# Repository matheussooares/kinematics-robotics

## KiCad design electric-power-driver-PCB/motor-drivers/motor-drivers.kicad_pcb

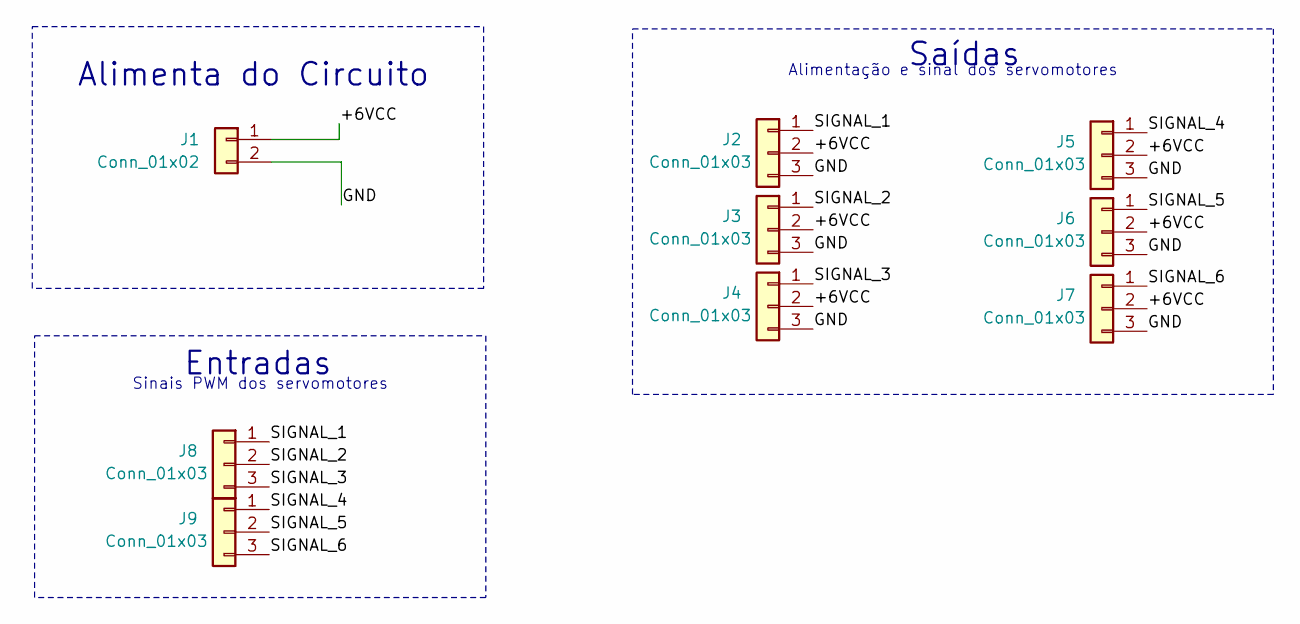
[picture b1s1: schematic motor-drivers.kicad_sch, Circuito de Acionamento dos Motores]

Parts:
J1: Conn_01x02; TerminalBlock_philmore_TB132
J2, J3, J4, J5, J6, J7, J8, J9: Conn_01x03; TerminalBlock_philmore_TB133

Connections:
/+6VCC: J1.1, J2.2, J3.2, J4.2, J5.2, J6.2, J7.2
/GND: J1.2, J2.3, J3.3, J4.3, J5.3, J6.3, J7.3
/SIGNAL_1: J2.1, J8.1
/SIGNAL_2: J3.1, J8.2
/SIGNAL_3: J4.1, J8.3
/SIGNAL_4: J5.1, J9.1
/SIGNAL_5: J6.1, J9.2
/SIGNAL_6: J7.1, J9.3

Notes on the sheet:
Alimentação e sinal dos servomotores
Sinais PWM dos servomotores
Alimenta do Circuito
Entradas
Saídas

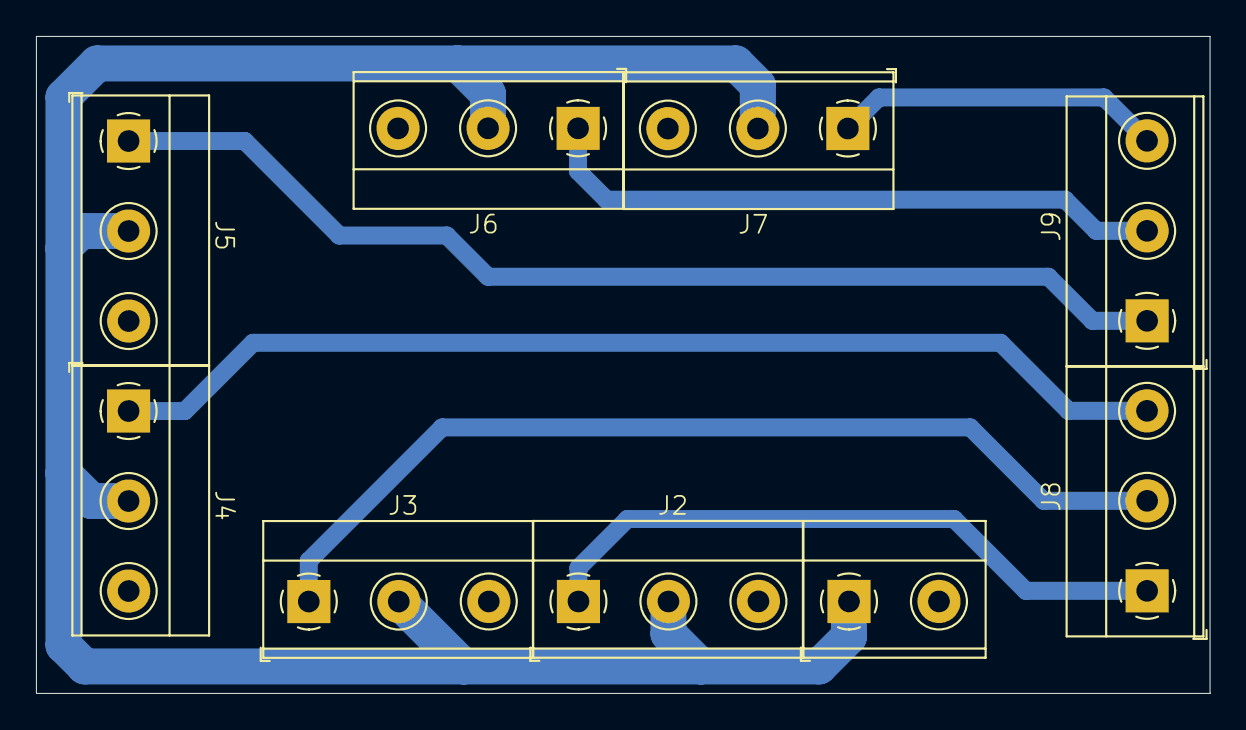
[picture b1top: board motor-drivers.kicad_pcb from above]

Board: 2 copper layers, 65.2 x 36.5 mm, 9 parts (0 on the bottom side), 8 nets.

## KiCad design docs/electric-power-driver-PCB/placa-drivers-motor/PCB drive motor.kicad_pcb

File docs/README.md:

# Cinemática de um robô didático

O cálculo da cinemática inversa é um desafio na robótica, especialmente para manipuladores robóticos, e métodos tradicionais muitas vezes não são eficazes.
Este trabalho foca na solução da cinemática inversa de um robô manipulador didático com 5 graus de liberdade (DoF), disponível no laboratório da UFC, utilizando algoritmos de aprendizado de máquina com foco em abordagens de modelos locais e globais.

Especificamente, foram empregadas redes neurais Perceptron Multicamadas e o algoritmo K-means para os modelos locais segmentarem o espaço operacional. Inicialmente, a modelagem da cinemática direta é  realizada, utilizando a notação de Denavit-Hartenberg, de modo a gerar um banco de dados contendo informações do espaço cartesiano e do espaço das juntas do manipulador. Este banco de dados é então filtrado, removendo amostras inalcançáveis e amostras próximas entre si no  espaço cartesiano. A fase de otimização de hiperparâmetros para os modelos globais envolveu ajustar a melhor arquitetura das redes neurais, e para os modelos locais abrangeu determinar o número ````k```` de clusters que melhor dividisse o espaço operacional. A avaliação de desempenho dos algoritmos é feita com base nas medidas ````R²```` e ````MSE````, tanto no espaço das juntas como no espaço cartesiano, e os resultados obtidos evidenciam que ambas as abordagens se mostraram viáveis para a tarefa em questão, com a abordagem local superando a global.

## Requisitos

````
pip install -r requirements.txt
````

## Objetivo

O objetivo geral do trabalho consiste na aproximação da cinemática inversa de um robô manipulador didático através de algoritmos de aprendizado de máquina. Por isso, os seguintes objetivos específicos foram traçados:

- Estudar métodos para geração da cinemática direta de um manipulador robótico;
- Investigar dados relevantes que relacionem os ângulos das juntas com a posição cartesianas para fins de treinamento dos modelos de aprendizado de máquina;
- Pesquisar modelos de regressão para aproximação de cinemática inversa; 
- Investigar métodos de avaliação para os modelos que solucionam a cinemática inversa.

## Máterias e métodos

O braço robótico trata-se de um robô do tipo manipulador, desenvolvido em um módulo didático pelo grupo de pesquisa em robótica do [IFCE](https://robotica.ifce.edu.br/). Sua fabricação foi realizada por meio de uma impressora 3D, utilizando filamento de PLA, um material de baixo custo amplamente empregado em impressões tridimensionais.

<div align="center">
  
  <br>
  <em>Figura 1: Braço robótico didático</em>
</div>

### Modelagem Direta do Manipulador

A estrutura mecânica do braço é composta por cinco partes físicas interligadas por cinco juntas rotacionais (5 GDL), definindo o robô como um modelo 5𝑅.

<div align="center">
  
  <br>
  <em>Figura 2: Estrutura do braço robótico didático</em>
</div>

Devido ao mecanismo robótico ser constituido por 5 graus de liberdade de juntas rotativas, a cadeia cinemática possui cinco variáveis de juntas $\theta_{i}$, para $i = 1,...,5$. Utilizando as regras e etapas do método de Denavit-Hartenberg são fixados os sistemas de referência locais em cada elemento do robô e levantado os seus parâmetro D-H.

<div align="center">
  
  <br>
  <em>Figura 3: Sistema de coordenadas locais do manipulador didático</em>
</div>

A descrição da cinemática direta desse sistema está apresentada na Tabela abaixo, no qual define os parâmetros de Denavit-Hartenberg de cada elemento do manipulador.

| i | $\theta$ ($^\circ$) | $a$ ($cm$) | $d$ ($cm$) | $\alpha$ ($^\circ$) |
|---|----------------------|------------|------------|---------------------|
| 1 | $\theta_{1}$         | $0$         | $Elo_{0}$      | $+90$           |
| 2 | $\theta_{2}$         | $Elo_{1}$      | $0$           | $+180$        |
| 3 | $\theta_{3}$         | $Elo_{2}$      | $0$           | $-180$        |
| 4 | $\theta_{4} + 90$    | $0$           | $0$           | $+90$          |
| 5 | $\theta_{5}$         | $0$           | $Elo_{3}+ Elo_{4}$ | $0$       |

A validação da cinemática direta foi conduzida inserindo a parametrização D-H no modelo do braço robótico desenvolvido na biblioteca Robotics Toolbox for Python.

<div align="center">
  
  <br>
  <em>Figura 4: Simulação da modelagem direta do manipulador didático</em>
</div>

### Padrões de Treinamento

O método para geração dos padrões de treinamento passa pela modelagem da cinemática direta do manipulador. A base de dados representa todo o volume de trabalho e o comportamento dos ângulos das juntas do robô realizando o mapeamento das relações entre o espaço operacional e o espaço das juntas.

<div align="center">
  
  <br>
  <em>Figura 5: Volume de trabalho do manipulador didático</em>
</div>

A base de dados bruta possui $33275$ observações. A decisão de fixar $\theta_{5}=0$, por influenciar na orientação do efetuador, simplificou a geração dos padrões. A distribuição no número de amostras por junta 𝑁 permitiu uma cobertura eficaz dos eixos. O ângulo $\theta_{1}$ otimizou a exploração do espaço $(𝑥,𝑦)$ e os outros ângulos balancearam o eixo $𝑧$. Considerando $𝑁 = 25$ obteve-se um total de $456976$ amostras. Com as resoluções houve uma redução de $91,5\%$;

A ausência de tratamento nos dados pode gerando a construção de modelos pouco fiéis, aumento dos custos computacionais e dificuldade do modelo em entender os padrões de treinamento (Faceli, 2011). E por conta dos aspectos não lineares, as singularidades e as soluções mal postas das equações, levantarem a existências de múltiplas soluções, nenhuma solução ou soluções não admissíveis nas posições do efetuador (MELO, 2015), é definido um conjunto de pré-processamento dos dados.

Para um raio de similaridade de $𝑟_{𝑠}=1 𝑐𝑚$, a base de dados final passou a conter $6890$ amostras, representando uma redução de 20,7% dos dados originais. Contêm atributos de entradas que descrevem a posição $(𝑥,𝑦,𝑧)$ e as orientações Roll, Pitch e Yaw (𝜑,𝛽,𝜓) do efetuador no espaço tridimensional.

<div align="center">
  
  <br>
  <em>Figura 6: Volume de trabalho do manipulador sem redundâncias</em>
</div>

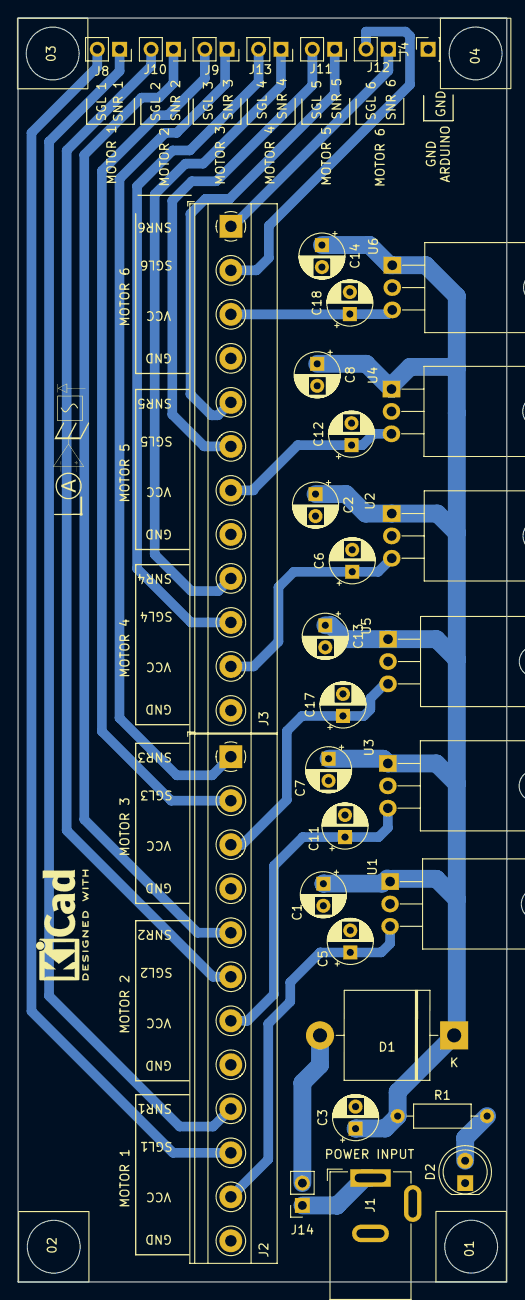
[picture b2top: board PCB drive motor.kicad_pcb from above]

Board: 2 copper layers, 55.5 x 143.6 mm, 37 parts (0 on the bottom side), 23 nets.

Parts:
01, 02, 03, 04: Furo
C1, C2, C7, C8, C13, C14: 10uF/50V; CP_Radial_D5.0mm_P2.50mm
C3, C5, C6, C11, C12, C17, C18: 1uF/50V; CP_Radial_D5.0mm_P2.50mm
D1: 1N5404; D_DO_6A6_DC__P15.24mm_Horizontal_D1.0mm
D2: LED; LED_D5.0mm
J1: CONN_ALIMENTAÇÃO_12V; BarrelJack_GCT_DCJ200-10-A_Horizontal
J2: Conn_motores_01_03; TerminalBlock_Phoenix_MKDS-1,5-12_1x12_P5.00mm_Horizontal
J3: Conn_motores_04_06; TerminalBlock_Phoenix_MKDS-1,5-12_1x12_P5.00mm_Horizontal
J4: Conn_GND_arduino; PinSocket_1x01_P2.54mm_Vertical
J8: CONN_IN/OU_1; PinSocket_1x02_P2.54mm_Vertical
J9: CONN_IN/OU_3; PinSocket_1x02_P2.54mm_Vertical
J10: CONN_IN/OU_2; PinSocket_1x02_P2.54mm_Vertical
J11: CONN_IN/OU_4; PinSocket_1x02_P2.54mm_Vertical
J12: CONN_IN/OU_6; PinSocket_1x02_P2.54mm_Vertical
J13: CONN_IN/OU_5; PinSocket_1x02_P2.54mm_Vertical
J14: LIGA/DESLIGA; PinSocket_1x02_P2.54mm_Vertical
R1: 1K; R_Axial_DIN0207_L6.3mm_D2.5mm_P10.16mm_Horizontal
U1, U2, U3, U5: LM7806_TO220; TO-220-3_Horizontal_TabDown
U4, U6: LM7805_TO220; TO-220-3_Horizontal_TabDown

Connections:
/12V: C1.1, C2.1, C3.1, C7.1, C8.1, C13.1, C14.1, D1.1 (K), R1.1, U1.1 (VI), U2.1 (VI), U3.1 (VI), U4.1 (VI), U5.1 (VI), U6.1 (VI)
/SENSOR_1: J2.9, J8.1
/SENSOR_2: J2.5, J10.1
/SENSOR_3: J2.1, J9.1
/SENSOR_4: J3.9, J11.1
/SENSOR_5: J3.5, J13.1
/SENSOR_6: J3.1, J12.1
/SIGNAL_1: J2.10, J8.2
/SIGNAL_2: J2.6, J10.2
/SIGNAL_3: J2.2, J9.2
/SIGNAL_4: J3.10, J11.2
/SIGNAL_5: J3.6, J13.2
/SIGNAL_6: J3.2, J12.2
/VCC5V_5: C12.1, J3.7, U4.3 (VO)
/VCC5V_6: C18.1, J3.3, U6.3 (VO)
/VCC6V_1: C5.1, J2.11, U1.3 (VO)
/VCC6V_2: C11.1, J2.7, U3.3 (VO)
/VCC6V_3: C17.1, J2.3, U5.3 (VO)
/VCC6V_4: C6.1, J3.11, U2.3 (VO)
GNDREF: C1.2, C2.2, C3.2, C5.2, C6.2, C7.2, C8.2, C11.2, C12.2, C13.2, C14.2, C17.2, C18.2, D2.1 (K), J1.2, J2.4, J2.8, J2.12, J3.4, J3.8, J3.12, J4.1, U1.2 (GND), U2.2 (GND), U3.2 (GND), U4.2 (GND), U5.2 (GND), U6.2 (GND)
unnamed: D1.2 (A), J14.2
unnamed: D2.2 (A), R1.2
unnamed: J1.1, J14.1

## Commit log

2024-04-04 add: structure of the application
2024-04-04 add: mdule plot
2024-04-04 add: mdule class forwaerd kinematic
2024-04-04 add: mdule preprocessing database
2024-04-04 add: main
2024-04-04 add: pycache
2024-04-04 update: pycache
2024-04-04 add: test
2024-04-04 add: dataset raw
2024-04-04 updata: main
2024-04-04 updata: forwardkinematics
2024-04-04 update: prepocessing dataset
2024-04-04 update: preprocessing dataset
2024-04-06 update: add remove_redundancy
2024-04-06 add: gitignore
2024-04-06 update: add full version forwardkinematics.ipynb
2024-04-06 add: datasets to ready
2024-04-06 update: readme
2024-04-06 add: figs and update readme
2024-04-09 Add files via upload
    add: transforms dataset
2024-04-09 update: pich, roll e yaw
2024-04-09 update: forwardkinematics concat
2024-04-16 add: createdataset
2024-04-16 Update: main
2024-04-18 update: function mapping
2024-04-18 update preprocessing: add func rotations
2024-04-18 update: preprocessing
2024-04-19 update: move datasets for raw
2024-04-19 update: preprocessingdatabase
2024-04-19 update: main add func remove_redundancy
2024-04-19 update: main add func rotations
2024-04-19 update: add dataset ready
2024-04-22 update: rename scripts to kinematicsrobotics
2024-04-22 update: rename and cd ETL
2024-04-22 add main AM
2024-04-22 add: pynb to AM
2024-04-22 update: rename ETL
2024-04-22 update: machine learning
2024-05-02 update: forwardkinematics
2024-05-02 update: forwardkinematics comment
2024-05-03 update: struct project
2024-05-03 update: dataprocessind and main
2024-05-03 update: struct
2024-05-04 update: dataprocessing commit
2024-05-04 update: factory forwardkinematics
2024-05-04 update: gitignore
2024-05-04 update: spacemapping and forwardkinematics
2024-05-04 update: gitignore final
2024-05-04 add: geral to debugg, update: rename forwardkinematics to forward, update: clear all code main
2024-05-04 update: rename ETL to forwardkinematics
2024-05-04 update: fixed bug function neighbors
2024-05-04 update: remove geral and test in main
2024-05-04 update: kinematic test
2024-05-05 update: function rotations
2024-05-05 update: remove testkinematics
2024-05-05 update: dell data.raw and add load and create funct save
2024-05-06 update: add func save.dataframe in main
2024-05-06 update: change dataframe in module load
2024-05-06 update: def new struct model project
2024-05-06 update: forwardkinematics "-finished
2024-05-07 update: data raw end data ready
2024-05-07 update: improvement spacemapping and dataprocessing performance
2024-05-07 update: data dataset-radius-0.7cm
2024-05-07 update: add best practices
2024-05-07 update: dateset radius 0.7cm 1.25cm 1cm
2024-05-07 update: dateset radius 1.5cm
2024-05-08 add: script data analytics
2024-05-08 update: rename load to datahandler
2024-05-08 update: rename plot to plottingutils add new structs
2024-05-08 add: img space operational
2024-05-09 add: inversekinematics
2024-05-11 update: add modelmlp
2024-05-13 update: machine learning struct
2024-05-13 update: model mlp and machinelearning
2024-05-15 update machine learning
2024-05-16 update struct project machine learning
2024-05-17 update machine learning refactored
2024-05-21 update add GridSearch
2024-05-28 add space hidden, MLP
2024-05-30 update estimação de hiperparâmetros
2024-05-31 update machine learning and add history
2024-05-31 add metrics, model
2024-05-31 update struct
2024-06-03 update history hiper
2024-06-05 update history hiperparameter
2024-06-06 update history
2024-06-11 update train e test models
2024-06-15 update change name Forward Kinematics
2024-07-01 update class robo
2024-07-01 update new space mapping
2024-07-02 update kinematics
2024-07-02 update space mapping and kinematics
2024-07-02 update data processing
2024-07-04 update plot and handler
2024-07-08 update utils plots
2024-07-08 update metrics model
2024-07-10 update models, dataprocessing and machine learning
2024-07-12 update DataPreprocessing
2024-07-12 update class Preprocessing, Metric and module inverse kinematics
2024-07-16 update matrics
2024-07-17 update metric mse operational
2024-07-18 update noise metrics
2024-07-19 update robotic mapping, mse operaticio and test mse
2024-07-19 update readme and metrics machine learning
2024-07-22 add ParameterSearchMLP and update ParameterOptimizer
2024-07-23 add robotic manipulator 3D
2024-07-29 update hiperparameters
2024-07-30 update analytics and plotting utils
2024-07-30 update ParameterSearchMLP
2024-07-30 update models and ParameterSearchMLP
2024-08-03 update data save, hiperparams and RandomizedSearch
2024-08-05 update crossvalidation
2024-08-06 update add dataset split
2024-08-06 update data split
2024-08-07 add: electric power driver PCB update: 3D model robotic
2024-08-07 update: name hyperparameter-optimization
2024-08-07 update: test hyperparameter optimization
2024-08-07 Create LICENSE
2024-08-08 update hyperparameter
2024-08-12 update: scoring, save data split, init ParameterSearchMLP and scoring method RandomizedSearch
2024-08-12 update space grid search
2024-08-12 update notebook and crossvalidation model
2024-08-13 update cv_results
2024-09-10 update: plotings add: metod test k-means
2024-09-10 update: k-means e edit mlp-otimization
2024-09-11 update: mlp global add: kmeans
2024-09-11 update: mlp global, history mlp global
2024-09-11 update kmeans, data split
2024-09-16 update kmeans model
2024-09-16 update: k-means 6 clusters add: test model mlp local
2024-09-17 update: model local mlp
2024-09-17 add: PCB power driver motor
2024-09-19 add: forward toolboox
2024-09-19 update: plot utils
2024-09-23 update: analytics
2024-09-23 update: k-means 4 clusters add: test model mlp local
2024-09-24 add: requirements
2024-09-25 update analytics
2024-10-09 update:kmeans
2024-10-17 add cod motores
2024-10-17 update new project structure
2024-10-28 update: img and readme
2024-11-26 add: pcb motor drivers
2024-11-28 update: gebers placa
2024-12-10 update schema pcb and gerbers
2025-02-12 update: PCB
2025-02-12 move data split
2025-02-12 rename paste data splits
2025-02-13 update model, cross validation, data processing
2025-02-13 update embedded
2025-02-26 update: Random search model local
2025-02-28 update: random search model local result
2025-03-01 update: model local
